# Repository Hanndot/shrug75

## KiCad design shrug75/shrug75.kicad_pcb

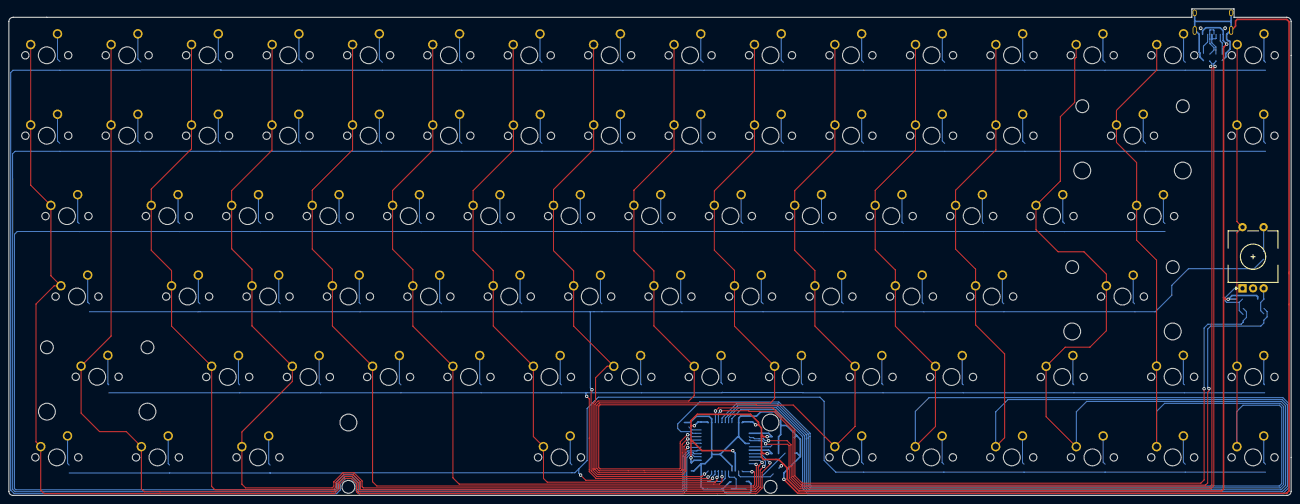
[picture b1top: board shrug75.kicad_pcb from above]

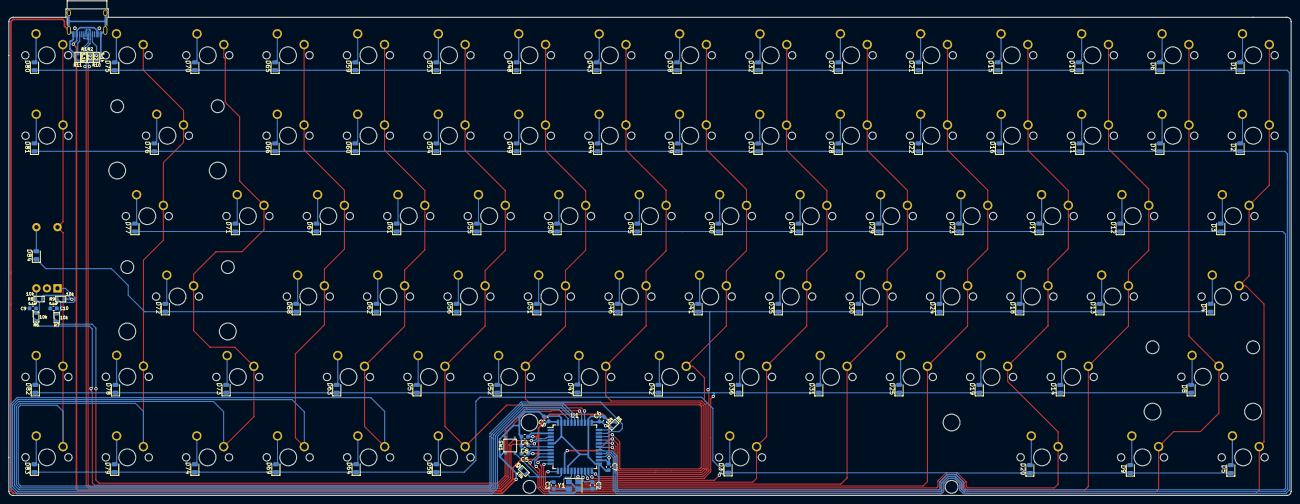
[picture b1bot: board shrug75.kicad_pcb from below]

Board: 2 copper layers, 303.8 x 115.3 mm, 190 parts (107 on the bottom side), 122 nets.

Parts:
A1: MX-NoLED; MXOnly-1U-NoLED
APOS1: MX-NoLED; MXOnly-1U-NoLED
B1: MX-NoLED; MXOnly-1U-NoLED
BACKSLASH1: MX-NoLED; MXOnly-1U-NoLED
BACKSPACE1: MX-NoLED; MXOnly-2U-NoLED
BACKTICK1: MX-NoLED; MXOnly-1U-NoLED
C1, C4, C5, C6, C9, C10: 0.1uF; C_0603_1608Metric
C2, C3: 22pF; C_0603_1608Metric
C7: 10uF; C_0603_1608Metric
C8: 1uF; C_0603_1608Metric
CAPSLOCK1: MX-LED; MXOnly-1U-NoLED
COMA1: MX-NoLED; MXOnly-1U-NoLED
C_KEY1: MX-NoLED; MXOnly-1U-NoLED
D1, D2, D3, D4, D5, D6, D7, D8, D9, D10, D11, D12, D13, D14, D15, D16, D17, D18, D19, D20, D21, D22, D23, D24, D25, D27, D28, D29, D30, D31, D32, D33, D34, D35, D36, D37, D38, D39, D40, D41, D42, D43, D44, D45, D46, D47, D48, D49, D50, D51, D52, D53, D54, D55, D56, D57, D58, D59, D60, D61, D62, D63, D64, D65, D66, D67, D68, D69, D70, D71, D72, D73, D74, D75, D76, D77, D78, D79, D80, D81, D82, D83, D84: D_Small; D_0805_2012Metric
DELETE1: MX-NoLED; MXOnly-1U-NoLED
DOT1: MX-NoLED; MXOnly-1U-NoLED
DOWN1: MX-NoLED; MXOnly-1U-NoLED
D_KEY1: MX-NoLED; MXOnly-1U-NoLED
E1: MX-NoLED; MXOnly-1U-NoLED
EIGHT1: MX-NoLED; MXOnly-1U-NoLED
END1: MX-NoLED; MXOnly-1U-NoLED
ENTER1: MX-NoLED; MXOnly-2U-NoLED
EQUAL1: MX-NoLED; MXOnly-1U-NoLED
ESC1: MX-NoLED; MXOnly-1U-NoLED
F1, F2, F3, F4, F5, F6, F7, F8, F9, F10, F11, F12: MX-NoLED; MXOnly-1U-NoLED
FIVE1: MX-NoLED; MXOnly-1U-NoLED
FN1: MX-NoLED; MXOnly-1U-NoLED
FOUR1: MX-NoLED; MXOnly-1U-NoLED
F_KEY1: MX-NoLED; MXOnly-1U-NoLED
G1: MX-NoLED; MXOnly-1U-NoLED
H1: MX-NoLED; MXOnly-1U-NoLED
HOME1: MX-NoLED; MXOnly-1U-NoLED
I1: MX-NoLED; MXOnly-1U-NoLED
INSERT1: MX-NoLED; MXOnly-1U-NoLED
J1: MX-NoLED; MXOnly-1U-NoLED
J2: USB_C_Receptacle_USB2.0; USB_C_Receptacle_HRO_TYPE-C-31-M-12
K1: MX-NoLED; MXOnly-1U-NoLED
L1: MX-NoLED; MXOnly-1U-NoLED
LEFT1: MX-NoLED; MXOnly-1U-NoLED
L_ALT1: MX-NoLED; MXOnly-1U-NoLED
L_BRACKET1: MX-NoLED; MXOnly-1U-NoLED
L_CTRL1: MX-NoLED; MXOnly-1U-NoLED
L_SHIFT1: MX-NoLED; MXOnly-2U-NoLED
M1: MX-NoLED; MXOnly-1U-NoLED
MINUS1: MX-NoLED; MXOnly-1U-NoLED
N1: MX-NoLED; MXOnly-1U-NoLED
NINE1: MX-NoLED; MXOnly-1U-NoLED
O1: MX-NoLED; MXOnly-1U-NoLED
ONE1: MX-NoLED; MXOnly-1U-NoLED
P1: MX-NoLED; MXOnly-1U-NoLED
PRTSC1: MX-NoLED; MXOnly-1U-NoLED
Q1: MX-NoLED; MXOnly-1U-NoLED
R1, R2: 22; R_0603
R3, R5, R6, R7, R8, R9: 10k; R_0603
R10, R11: 5.1k; R_0603
RIGHT1: MX-NoLED; MXOnly-1U-NoLED
R_ALT1: MX-NoLED; MXOnly-1U-NoLED
R_BRACKET1: MX-NoLED; MXOnly-1U-NoLED
R_CTRL1: MX-NoLED; MXOnly-1U-NoLED
R_KEY1: MX-NoLED; MXOnly-1U-NoLED
R_SHIFT1: MX-NoLED; MXOnly-1U-NoLED
S1: MX-NoLED; MXOnly-1U-NoLED
SEMICOLON1: MX-NoLED; MXOnly-1U-NoLED
SEVEN1: MX-NoLED; MXOnly-1U-NoLED
SIX1: MX-NoLED; MXOnly-1U-NoLED
SLASH1: MX-NoLED; MXOnly-1U-NoLED
SPACE1: MX-NoLED; MXOnly-6.25U-ReversedStabilizers-NoLED
SW1: SW_Push; SW_SPST_3x3
SW2: Rotary_Encoder_Switch; RotaryEncoder_EC11
T1: MX-NoLED; MXOnly-1U-NoLED
TAB1: MX-NoLED; MXOnly-1U-NoLED
THREE1: MX-NoLED; MXOnly-1U-NoLED
TWO1: MX-NoLED; MXOnly-1U-NoLED
U1: ATmega32U4-AU; TQFP-44_10x10mm_P0.8mm
UP1: MX-NoLED; MXOnly-1U-NoLED
U_KEY1: MX-NoLED; MXOnly-1U-NoLED
V1: MX-NoLED; MXOnly-1U-NoLED
W1: MX-NoLED; MXOnly-1U-NoLED
WIN1: MX-NoLED; MXOnly-1U-NoLED
X1: MX-NoLED; MXOnly-1U-NoLED
Y1: 16MHz; Crystal_SMD_3225-4Pin_3.2x2.5mm
Y_KEY1: MX-NoLED; MXOnly-1U-NoLED
Z1: MX-NoLED; MXOnly-1U-NoLED
ZERO1: MX-NoLED; MXOnly-1U-NoLED

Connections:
+5V: C1.1, C4.1, C5.1, C6.1, C7.1, J2.A4, J2.A9, J2.B4, J2.B9, R3.1, R8.2, R9.2, U1.2, U1.7, U1.14, U1.24, U1.34, U1.44
COL0: BACKTICK1.1, CAPSLOCK1.1, ESC1.1, L_CTRL1.1, TAB1.1, U1.8
COL1: F1.1, L_SHIFT1.1, ONE1.1, U1.9, WIN1.1
COL2: A1.1, F2.1, Q1.1, TWO1.1, U1.10, Z1.1
COL3: F3.1, L_ALT1.1, S1.1, THREE1.1, U1.11, W1.1, X1.1
COL4: C_KEY1.1, D_KEY1.1, E1.1, F4.1, FOUR1.1, U1.12
COL5: F5.1, FIVE1.1, F_KEY1.1, R_KEY1.1, U1.18, V1.1
COL6: B1.1, F6.1, G1.1, SIX1.1, SPACE1.1, T1.1, U1.19
COL7: F7.1, H1.1, N1.1, SEVEN1.1, U1.28, Y_KEY1.1
COL8: EIGHT1.1, F8.1, J1.1, M1.1, U1.29, U_KEY1.1
COL9: COMA1.1, F9.1, I1.1, K1.1, NINE1.1, U1.30
COL10: DOT1.1, F10.1, L1.1, O1.1, R_ALT1.1, U1.31, ZERO1.1
COL11: F11.1, FN1.1, MINUS1.1, P1.1, SEMICOLON1.1, SLASH1.1, U1.41
COL12: APOS1.1, EQUAL1.1, F12.1, L_BRACKET1.1, R_CTRL1.1, U1.40
COL13: ENTER1.1, INSERT1.1, LEFT1.1, R_BRACKET1.1, R_SHIFT1.1, U1.39
COL14: BACKSLASH1.1, BACKSPACE1.1, DOWN1.1, PRTSC1.1, U1.38, UP1.1
COL15: DELETE1.1, END1.1, HOME1.1, RIGHT1.1, SW2.S2, U1.32
D+: J2.A6, J2.B6, R1.2
D-: J2.A7, J2.B7, R2.2
D_N: R2.1, U1.3
D_P: R1.1, U1.4
EC11A: R7.1, R9.1, SW2.A
EC11A_M: C10.2, R7.2, U1.36
EC11B: R6.1, R8.1, SW2.B
EC11B_M: C9.1, R6.2, U1.37
GND: C1.2, C2.2, C3.2, C4.2, C5.2, C6.2, C7.2, C8.2, C9.2, C10.1, J2.A1, J2.A12, J2.B1, J2.B12, J2.S1, R5.1, R10.1, R11.1, SW1.1, SW2.C, U1.5, U1.15, U1.23, U1.35, U1.43, Y1.2, Y1.4
unnamed: A1.2, D13.2
unnamed: APOS1.2, D68.2
unnamed: B1.2, D36.2
unnamed: BACKSLASH1.2, D77.2
unnamed: BACKSPACE1.2, D76.2
unnamed: BACKTICK1.2, D2.2
unnamed: C8.1, U1.6
unnamed: CAPSLOCK1.2, D4.2
unnamed: COMA1.2, D52.2
unnamed: C_KEY1.2, D25.2
unnamed: D1.2, ESC1.2
unnamed: D3.2, TAB1.2
unnamed: D5.2, L_CTRL1.2
unnamed: D6.2, F1.2
unnamed: D7.2, ONE1.2
unnamed: D8.2, L_SHIFT1.2
unnamed: D9.2, WIN1.2
unnamed: D10.2, F2.2
unnamed: D11.2, TWO1.2
unnamed: D12.2, Q1.2
unnamed: D14.2, Z1.2
unnamed: D15.2, F3.2
unnamed: D16.2, THREE1.2
unnamed: D17.2, W1.2
unnamed: D18.2, S1.2
unnamed: D19.2, X1.2
unnamed: D20.2, L_ALT1.2
unnamed: D21.2, F4.2
unnamed: D22.2, FOUR1.2
unnamed: D23.2, E1.2
unnamed: D24.2, D_KEY1.2
unnamed: D27.2, F5.2
unnamed: D28.2, FIVE1.2
unnamed: D29.2, R_KEY1.2
unnamed: D30.2, F_KEY1.2
unnamed: D31.2, V1.2
unnamed: D32.2, F6.2
unnamed: D33.2, SIX1.2
unnamed: D34.2, T1.2
unnamed: D35.2, G1.2
unnamed: D37.2, SPACE1.2
unnamed: D38.2, F7.2
unnamed: D39.2, SEVEN1.2
unnamed: D40.2, Y_KEY1.2
unnamed: D41.2, H1.2
unnamed: D42.2, N1.2
unnamed: D43.2, F8.2
unnamed: D44.2, EIGHT1.2
unnamed: D45.2, U_KEY1.2
unnamed: D46.2, J1.2
unnamed: D47.2, M1.2
unnamed: D48.2, F9.2
unnamed: D49.2, NINE1.2
unnamed: D50.2, I1.2
unnamed: D51.2, K1.2
unnamed: D53.2, F10.2
unnamed: D54.2, ZERO1.2
unnamed: D55.2, O1.2
unnamed: D56.2, L1.2
unnamed: D57.2, DOT1.2
unnamed: D58.2, R_ALT1.2
unnamed: D59.2, F11.2
unnamed: D60.2, MINUS1.2
unnamed: D61.2, P1.2
unnamed: D62.2, SEMICOLON1.2
unnamed: D63.2, SLASH1.2
unnamed: D64.2, FN1.2
unnamed: D65.2, F12.2
unnamed: D66.2, EQUAL1.2
unnamed: D67.2, L_BRACKET1.2
unnamed: D69.2, R_CTRL1.2
unnamed: D70.2, INSERT1.2
unnamed: D71.2, R_BRACKET1.2
unnamed: D72.2, ENTER1.2
unnamed: D73.2, R_SHIFT1.2
unnamed: D74.2, LEFT1.2
unnamed: D75.2, PRTSC1.2
unnamed: D78.2, UP1.2
unnamed: D79.2, DOWN1.2
unnamed: D80.2, DELETE1.2
unnamed: D81.2, HOME1.2
unnamed: D82.2, END1.2
unnamed: D83.2, RIGHT1.2
unnamed: D84.2, SW2.S1
unnamed: J2.A5, R10.2
unnamed: J2.B5, R11.2
unnamed: R3.2, SW1.2, U1.13
unnamed: R5.2, U1.33
ROW0: D1.1, D6.1, D10.1, D15.1, D21.1, D27.1, D32.1, D38.1, D43.1, D48.1, D53.1, D59.1, D65.1, D70.1, D75.1, D80.1, U1.25
ROW1: D2.1, D7.1, D11.1, D16.1, D22.1, D28.1, D33.1, D39.1, D44.1, D49.1, D54.1, D60.1, D66.1, D76.1, D81.1, U1.26
ROW2: D3.1, D12.1, D17.1, D23.1, D29.1, D34.1, D40.1, D45.1, D50.1, D55.1, D61.1, D67.1, D71.1, D77.1, U1.27
ROW3: D4.1, D13.1, D18.1, D24.1, D30.1, D35.1, D41.1, D46.1, D51.1, D56.1, D62.1, D68.1, D72.1, D84.1, U1.22
ROW4: D8.1, D14.1, D19.1, D25.1, D31.1, D36.1, D42.1, D47.1, D52.1, D57.1, D63.1, D73.1, D78.1, D82.1, U1.21
ROW5: D5.1, D9.1, D20.1, D37.1, D58.1, D64.1, D69.1, D74.1, D79.1, D83.1, U1.20
XTAL1: C2.1, U1.17, Y1.1
XTAL2: C3.1, U1.16, Y1.3

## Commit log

2021-04-07 Innitial commit
2021-04-07 Adding kicad project
2021-04-07 Adding switch layout DXF file
2021-04-07 Adding submodules
2021-04-07 Adding libraries
2021-04-07 Adding some files
2021-04-07 Changing some stuff
2021-04-07 Adding edge cuts and switch layout
2021-04-07 Adding another .dxf~ file
2021-04-07 Adding more 2 files
2021-04-07 Adding another submodule
2021-04-07 Forgot these 2 files hehe
2021-04-07 Addin' all of these switches
2021-04-08 Placing diodes
2021-04-08 Defining keyboard matrix
2021-04-08 Defining usb connection
2021-04-08 Microcontroller connections and all that kinda stuff
2021-04-08 Connecting rotary encoder to mcu & connecting the forgotten gnd pins
2021-04-09 Associating symbols to footprints
2021-04-09 Placing the switches
2021-04-09 False commit hehe. I don't even know anymore
2021-04-10 Placing diodes to the corresponding swtiches
2021-04-11 Connecting switch matrix
2021-04-11 Changing cap and res footprint
2021-04-11 Connecting the rest
2021-04-11 Fixing syntax
2021-04-13 Fixing some track to close too pad
2021-04-15 Editing B.SilkS layer
